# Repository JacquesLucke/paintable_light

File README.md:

# Paintable Light

Goals:
* I want to learn to make custom PCBs.
* Try to design something that children can solder, paint on and turn into a nice looking small light.

[Schematic](https://jacqueslucke.github.io/paintable_light/paintable_light_schematic.pdf)

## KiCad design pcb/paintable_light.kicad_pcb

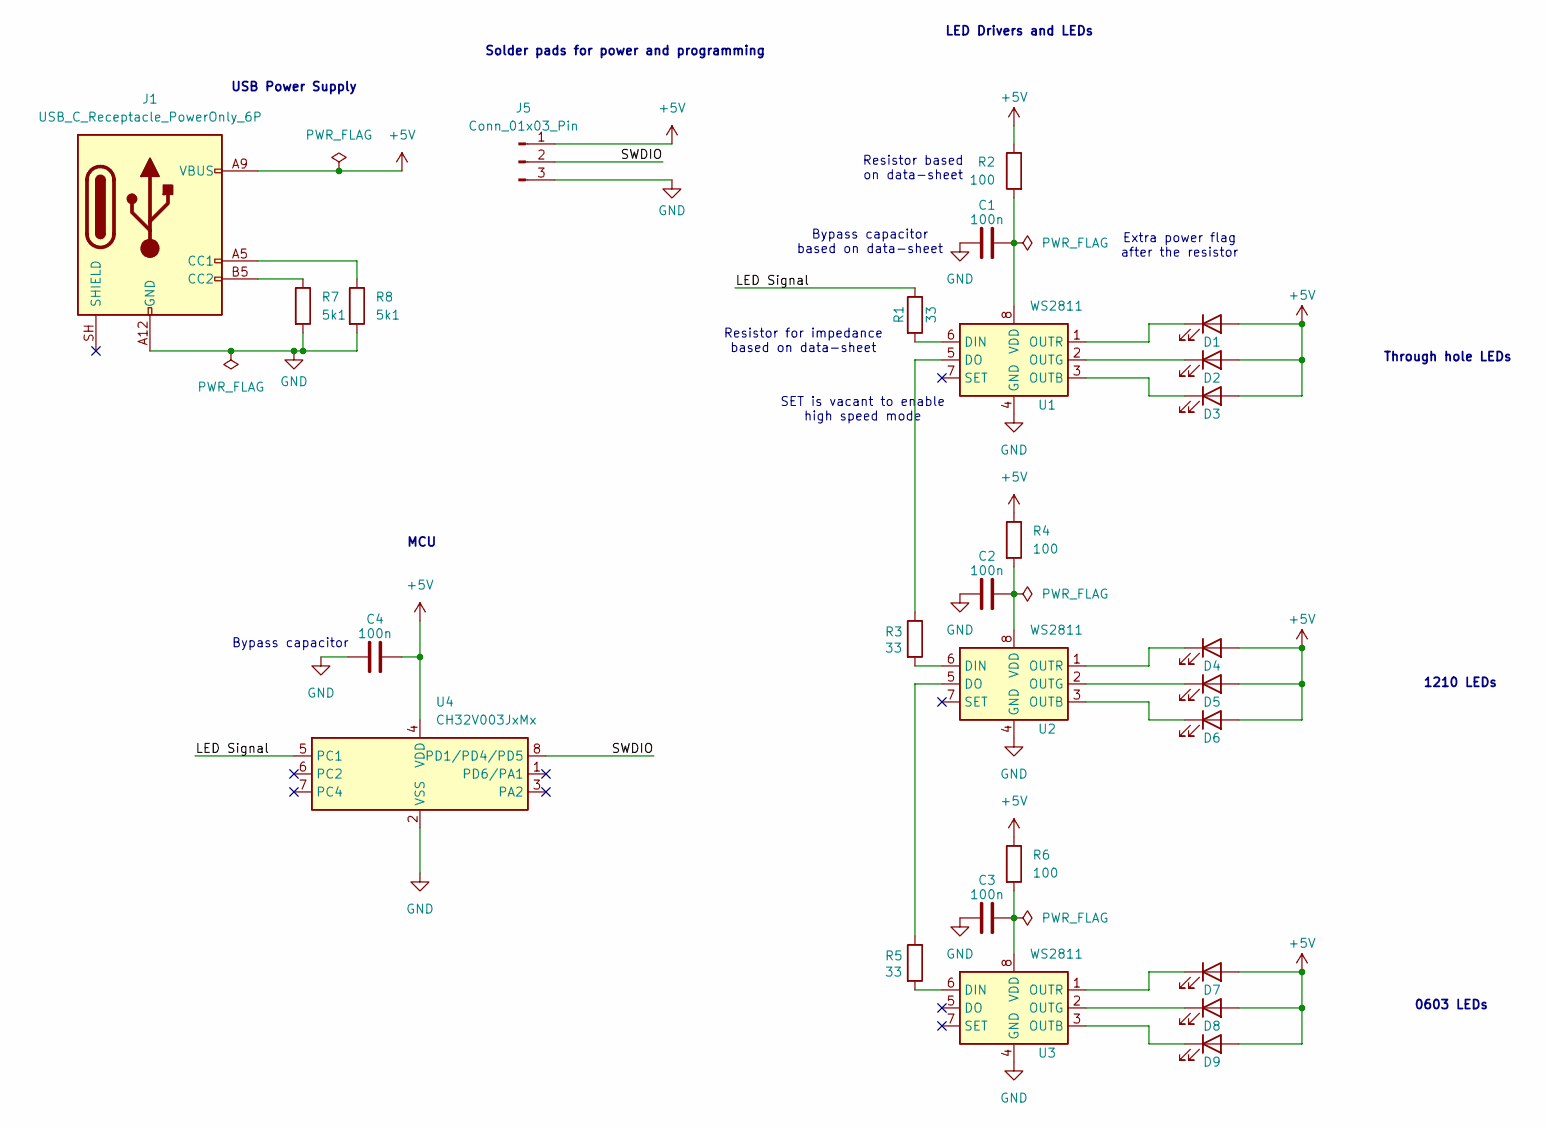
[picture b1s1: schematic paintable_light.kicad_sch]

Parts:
C1, C2, C3, C4: 100n; C_1206_3216Metric_Pad1.33x1.80mm_HandSolder
D1, D2, D3, D4, D5, D6, D7, D8, D9: LED; LED_1210_3225Metric_Pad1.42x2.65mm_HandSolder_front
J1: USB_C_Receptacle_PowerOnly_6P; usb_c_vertical_C5187465
J5: Conn_01x03_Pin; pin_header_flat_C41417360
R1, R3, R5: 33; R_1206_3216Metric_Pad1.30x1.75mm_HandSolder
R2, R4, R6: 100; R_1206_3216Metric_Pad1.30x1.75mm_HandSolder
R7, R8: 5k1; R_1206_3216Metric_Pad1.30x1.75mm_HandSolder
U1, U2, U3: WS2811; SOIC-8_3.9x4.9mm_P1.27mm
U4: CH32V003JxMx; JEITA_SOIC-8_3.9x4.9mm_P1.27mm

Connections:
+5V: C4.2, D1.2 (A), D2.2 (A), D3.2 (A), D4.2 (A), D5.2 (A), D6.2 (A), D7.2 (A), D8.2 (A), D9.2 (A), J1.A9 (VBUS), J1.B9 (VBUS), J5.1, R2.1, R4.1, R6.1, U4.4 (VDD)
/LED Signal: R1.1, U4.5 (PC1)
/SWDIO: J5.2, U4.8 (PD1/PD4/PD5)
GND: C1.1, C2.1, C3.1, C4.1, J1.A12 (GND), J1.B12 (GND), J5.3, R7.2, R8.2, U1.4 (GND), U2.4 (GND), U3.4 (GND), U4.2 (VSS)
unnamed: D1.1 (K), U1.1 (OUTR)
unnamed: D2.1 (K), U1.2 (OUTG)
unnamed: D3.1 (K), U1.3 (OUTB)
unnamed: D4.1 (K), U2.1 (OUTR)
unnamed: D5.1 (K), U2.2 (OUTG)
unnamed: D6.1 (K), U2.3 (OUTB)
unnamed: D7.1 (K), U3.1 (OUTR)
unnamed: D8.1 (K), U3.2 (OUTG)
unnamed: D9.1 (K), U3.3 (OUTB)
unnamed: J1.A5 (CC1), R8.1
unnamed: J1.B5 (CC2), R7.1
unnamed: R1.2, U1.6 (DIN)
unnamed: R3.1, U1.5 (DO)
unnamed: C1.2, R2.2, U1.8 (VDD)
unnamed: R3.2, U2.6 (DIN)
unnamed: R5.1, U2.5 (DO)
unnamed: C2.2, R4.2, U2.8 (VDD)
unnamed: R5.2, U3.6 (DIN)
unnamed: C3.2, R6.2, U3.8 (VDD)

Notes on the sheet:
Bypass capacitor based on data-sheet
Resistor based on data-sheet
SET is vacant to enable high speed mode
Bypass capacitor
Through hole LEDs
MCU
Resistor for impedance based on data-sheet
Extra power flag after the resistor
LED Drivers and LEDs
USB Power Supply
Solder pads for power and programming
1210 LEDs
0603 LEDs

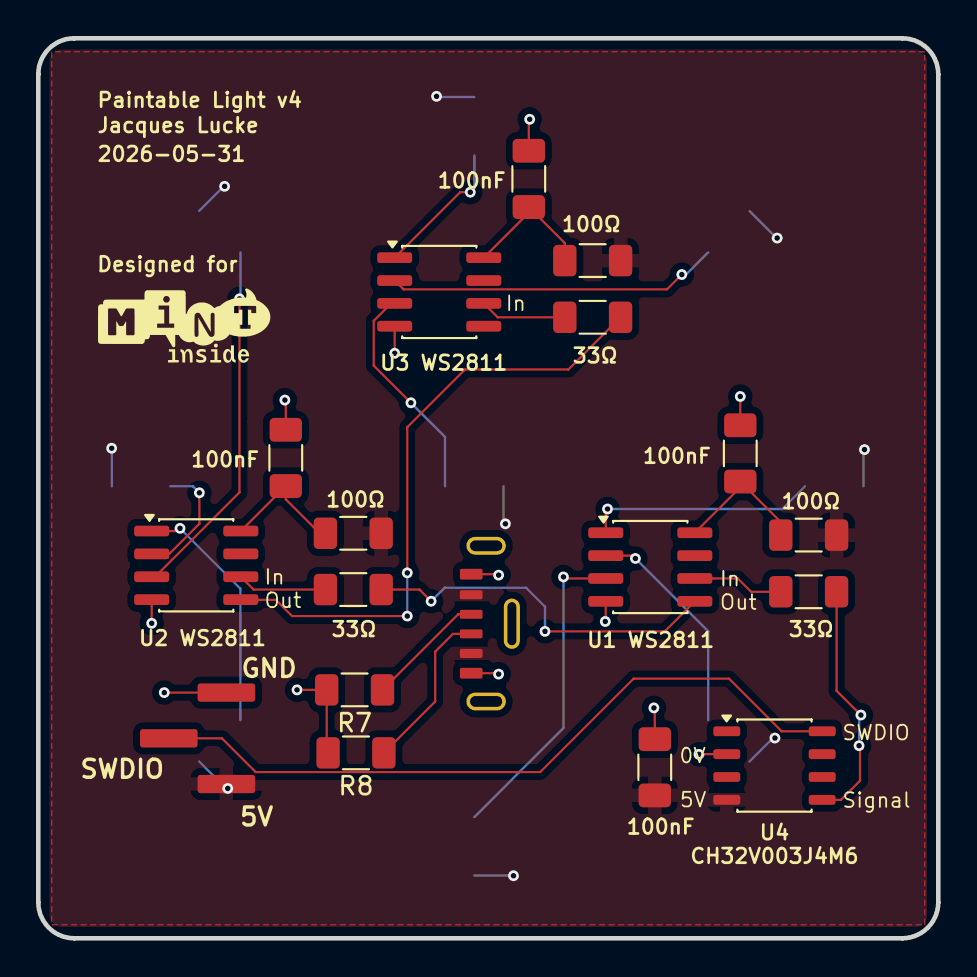
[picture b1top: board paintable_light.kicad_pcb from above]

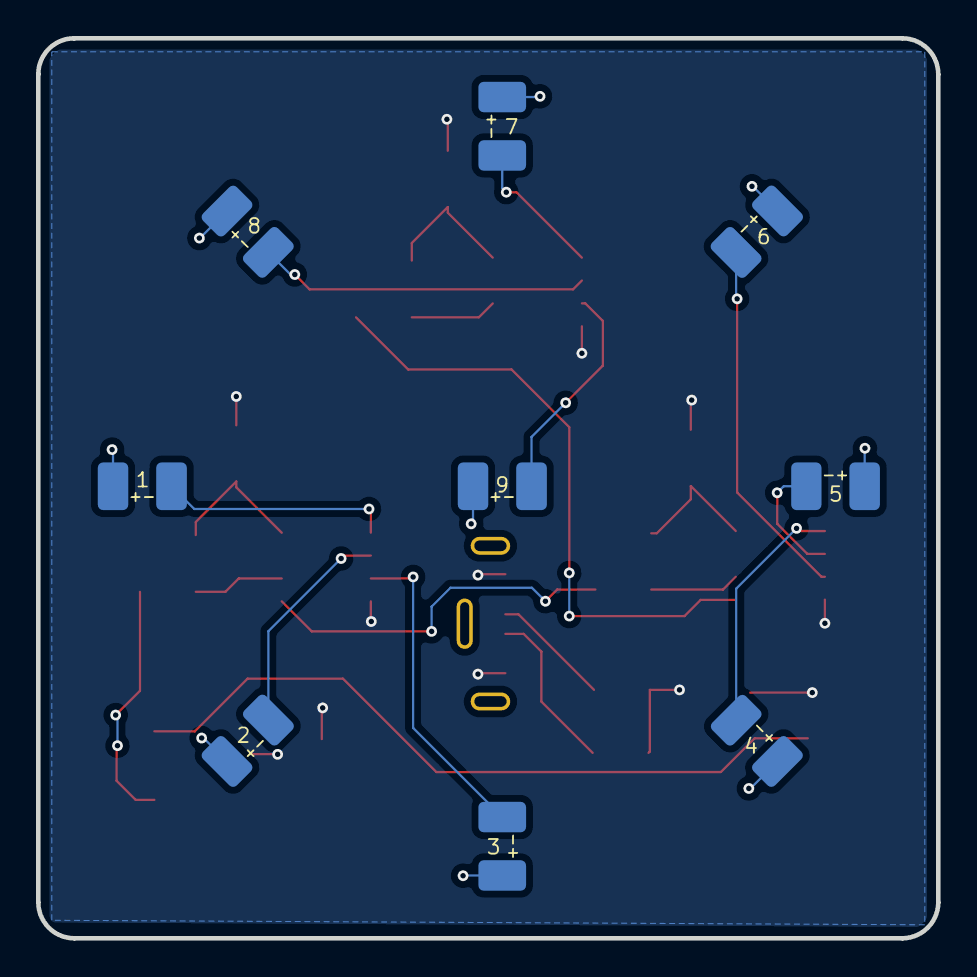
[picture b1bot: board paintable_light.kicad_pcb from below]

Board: 2 copper layers, 50.0 x 50.0 mm, 27 parts (9 on the bottom side), 23 nets.

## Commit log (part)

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2026-02-08 import jlcpcb settings
2026-02-08 maybe finished schematic
2026-02-08 initial layout
2026-02-08 update layout
2026-02-08 progress
2026-02-25 initial code
2026-02-26 add some notes
2026-02-27 initial production
2026-02-27 enable high speed
2026-02-27 initial new board layout
2026-03-13 update code for ch32v003
2026-03-13 github workflow
2026-03-13 improve signal
2026-03-25 update todos
2026-03-25 add note
